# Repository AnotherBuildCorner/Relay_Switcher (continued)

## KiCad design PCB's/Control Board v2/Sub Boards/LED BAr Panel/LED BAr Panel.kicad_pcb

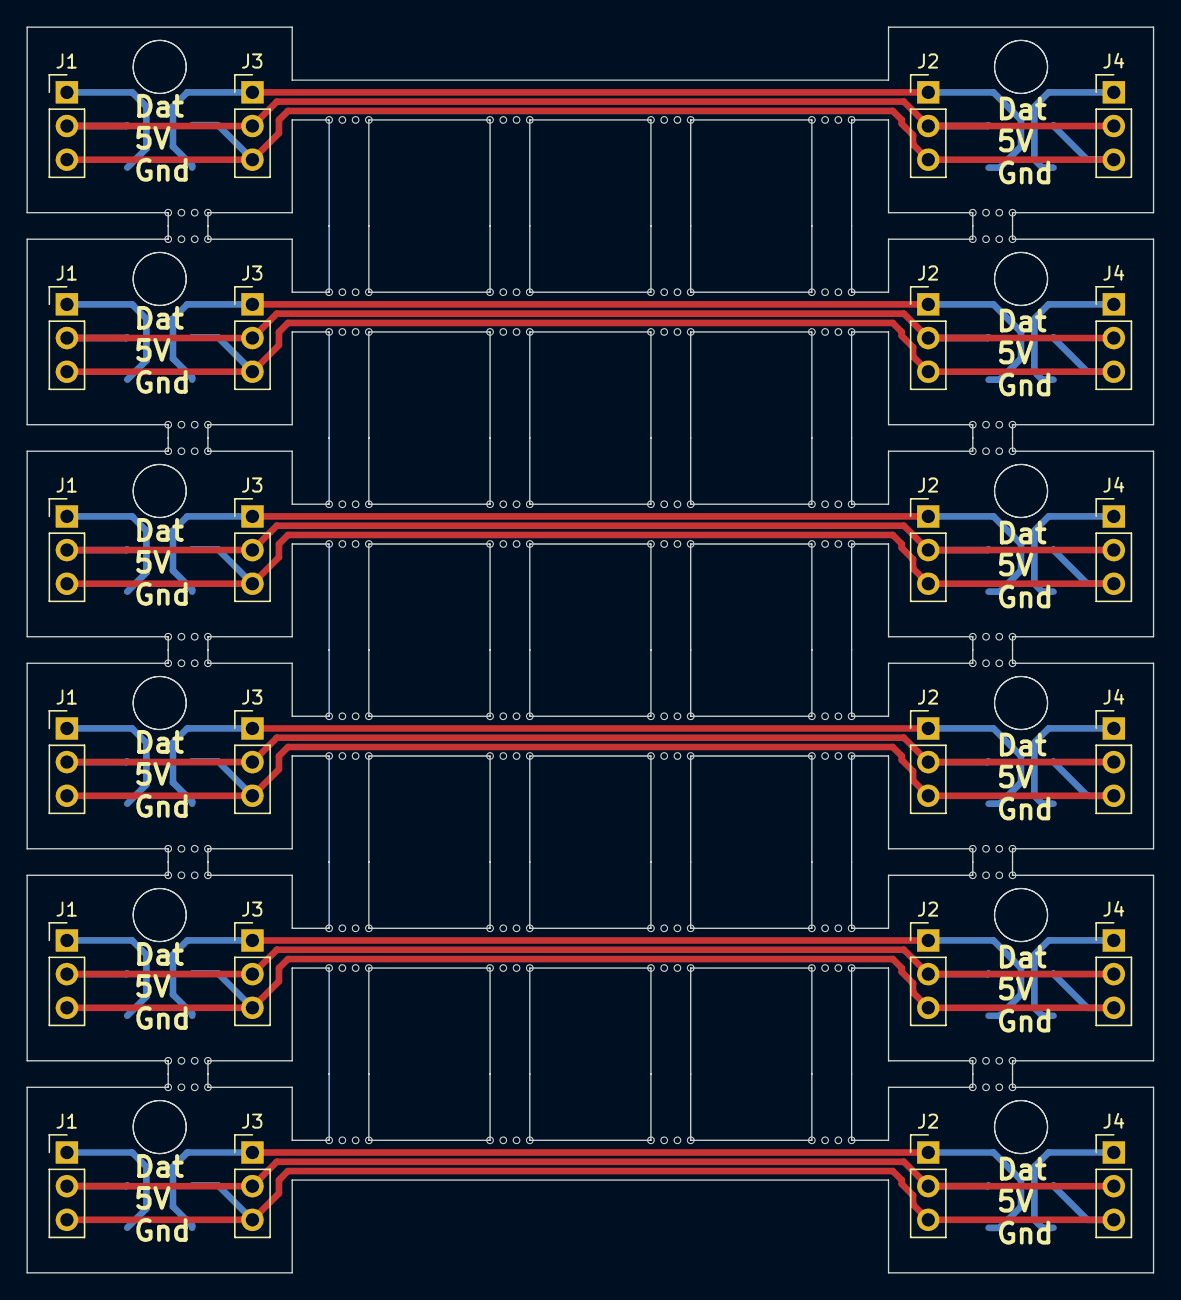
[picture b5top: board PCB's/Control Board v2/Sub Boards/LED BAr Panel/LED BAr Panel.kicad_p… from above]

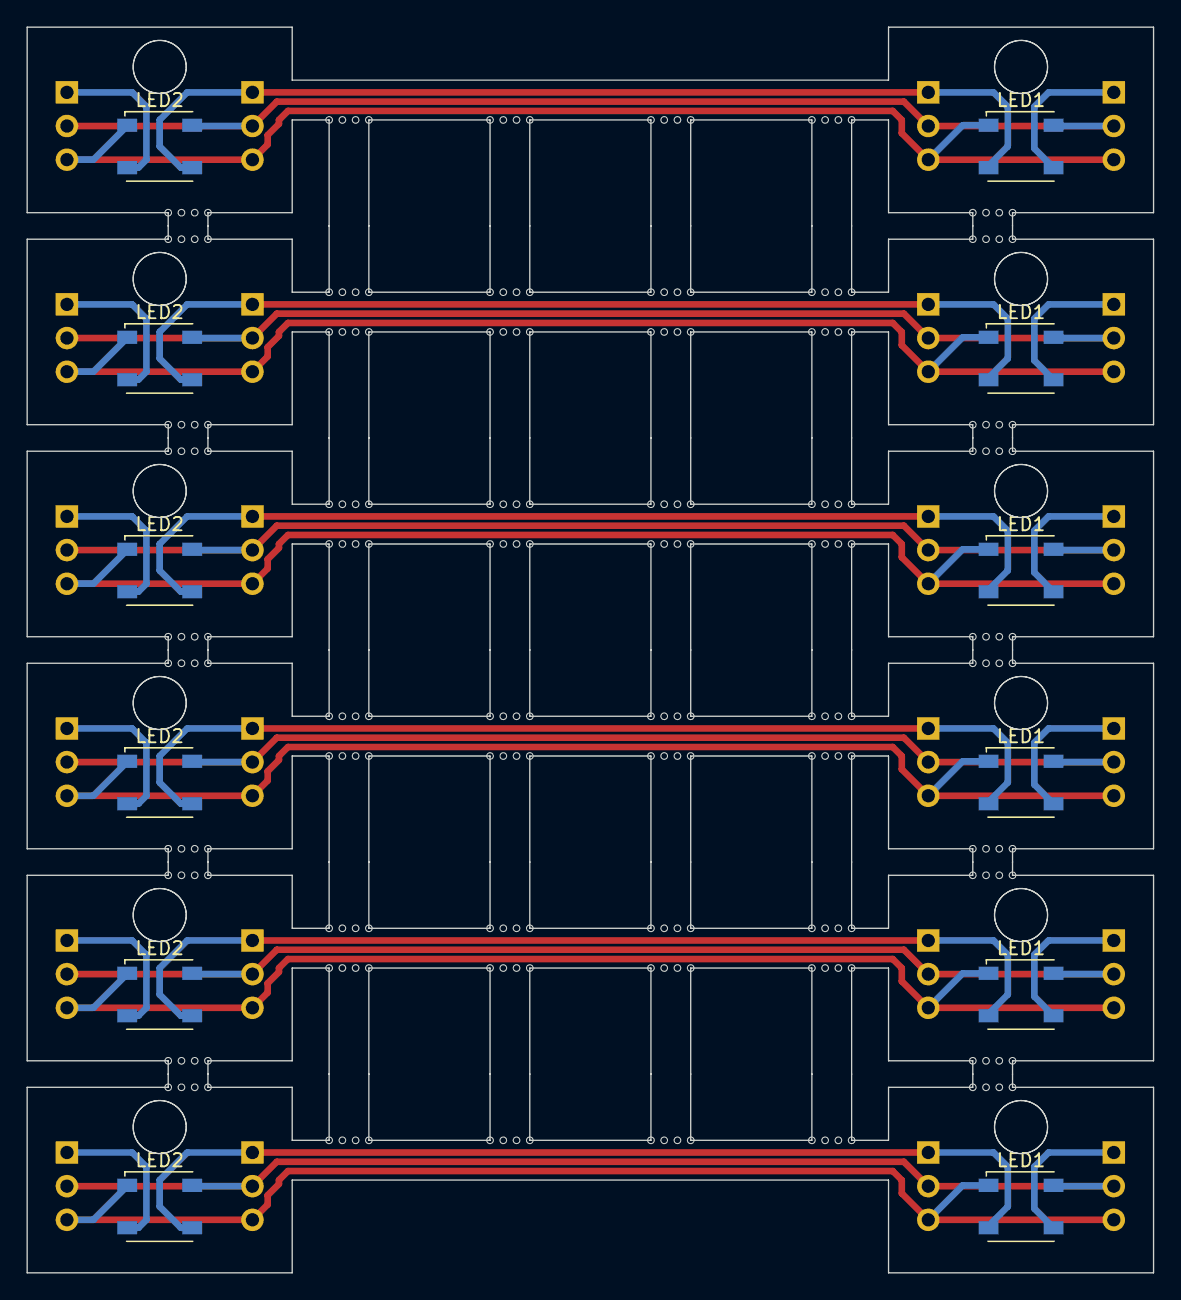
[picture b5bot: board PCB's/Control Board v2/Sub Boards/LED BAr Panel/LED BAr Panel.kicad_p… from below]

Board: 2 copper layers, 85.0 x 94.0 mm, 276 parts (12 on the bottom side), 30 nets.

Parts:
J1, J1#2, J1#3, J1#4, J1#5, J1#6, J3, J3#2, J3#3, J3#4, J3#5, J3#6: LED Strip Conn; PinHeader_1x03_P2.54mm_Vertical
J2, J2#2, J2#3, J2#4, J2#5, J2#6, J4, J4#2, J4#3, J4#4, J4#5, J4#6: Conn_01x03_Socket; PinHeader_1x03_P2.54mm_Vertical
KiKit_MB_1_1, KiKit_MB_1_2, KiKit_MB_1_3, KiKit_MB_1_4, KiKit_MB_2_1, KiKit_MB_2_2, KiKit_MB_2_3, KiKit_MB_2_4, KiKit_MB_3_1, KiKit_MB_3_2, KiKit_MB_3_3, KiKit_MB_3_4, KiKit_MB_4_1, KiKit_MB_4_2, KiKit_MB_4_3, KiKit_MB_4_4, KiKit_MB_5_1, KiKit_MB_5_2, KiKit_MB_5_3, KiKit_MB_5_4, KiKit_MB_6_1, KiKit_MB_6_2, KiKit_MB_6_3, KiKit_MB_6_4, KiKit_MB_7_1, KiKit_MB_7_2, KiKit_MB_7_3, KiKit_MB_7_4, KiKit_MB_8_1, KiKit_MB_8_2, KiKit_MB_8_3, KiKit_MB_8_4, KiKit_MB_9_1, KiKit_MB_9_2, KiKit_MB_9_3, KiKit_MB_9_4, KiKit_MB_10_1, KiKit_MB_10_2, KiKit_MB_10_3, KiKit_MB_10_4, KiKit_MB_11_1, KiKit_MB_11_2, KiKit_MB_11_3, KiKit_MB_11_4, KiKit_MB_12_1, KiKit_MB_12_2, KiKit_MB_12_3, KiKit_MB_12_4, KiKit_MB_13_1, KiKit_MB_13_2, KiKit_MB_13_3, KiKit_MB_13_4, KiKit_MB_14_1, KiKit_MB_14_2, KiKit_MB_14_3, KiKit_MB_14_4, KiKit_MB_15_1, KiKit_MB_15_2, KiKit_MB_15_3, KiKit_MB_15_4, KiKit_MB_16_1, KiKit_MB_16_2, KiKit_MB_16_3, KiKit_MB_16_4, KiKit_MB_17_1, KiKit_MB_17_2, KiKit_MB_17_3, KiKit_MB_17_4, KiKit_MB_18_1, KiKit_MB_18_2, KiKit_MB_18_3, KiKit_MB_18_4, KiKit_MB_19_1, KiKit_MB_19_2, KiKit_MB_19_3, KiKit_MB_19_4, KiKit_MB_20_1, KiKit_MB_20_2, KiKit_MB_20_3, KiKit_MB_20_4, KiKit_MB_21_1, KiKit_MB_21_2, KiKit_MB_21_3, KiKit_MB_21_4, KiKit_MB_22_1, KiKit_MB_22_2, KiKit_MB_22_3, KiKit_MB_22_4, KiKit_MB_23_1, KiKit_MB_23_2, KiKit_MB_23_3, KiKit_MB_23_4, KiKit_MB_24_1, KiKit_MB_24_2, KiKit_MB_24_3, KiKit_MB_24_4, KiKit_MB_25_1, KiKit_MB_25_2, KiKit_MB_25_3, KiKit_MB_25_4, KiKit_MB_26_1, KiKit_MB_26_2, KiKit_MB_26_3, KiKit_MB_26_4, KiKit_MB_27_1, KiKit_MB_27_2, KiKit_MB_27_3, KiKit_MB_27_4, KiKit_MB_28_1, KiKit_MB_28_2, KiKit_MB_28_3, KiKit_MB_28_4, KiKit_MB_29_1, KiKit_MB_29_2, KiKit_MB_29_3, KiKit_MB_29_4, KiKit_MB_30_1, KiKit_MB_30_2, KiKit_MB_30_3, KiKit_MB_30_4, KiKit_MB_31_1, KiKit_MB_31_2, KiKit_MB_31_3, KiKit_MB_31_4, KiKit_MB_32_1, KiKit_MB_32_2, KiKit_MB_32_3, KiKit_MB_32_4, KiKit_MB_33_1, KiKit_MB_33_2, KiKit_MB_33_3, KiKit_MB_33_4, KiKit_MB_34_1, KiKit_MB_34_2, KiKit_MB_34_3, KiKit_MB_34_4, KiKit_MB_35_1, KiKit_MB_35_2, KiKit_MB_35_3, KiKit_MB_35_4, KiKit_MB_36_1, KiKit_MB_36_2, KiKit_MB_36_3, KiKit_MB_36_4, KiKit_MB_37_1, KiKit_MB_37_2, KiKit_MB_37_3, KiKit_MB_37_4, KiKit_MB_38_1, KiKit_MB_38_2, KiKit_MB_38_3, KiKit_MB_38_4, KiKit_MB_39_1, KiKit_MB_39_2, KiKit_MB_39_3, KiKit_MB_39_4, KiKit_MB_40_1, KiKit_MB_40_2, KiKit_MB_40_3, KiKit_MB_40_4, KiKit_MB_41_1, KiKit_MB_41_2, KiKit_MB_41_3, KiKit_MB_41_4, KiKit_MB_42_1, KiKit_MB_42_2, KiKit_MB_42_3, KiKit_MB_42_4, KiKit_MB_43_1, KiKit_MB_43_2, KiKit_MB_43_3, KiKit_MB_43_4, KiKit_MB_44_1, KiKit_MB_44_2, KiKit_MB_44_3, KiKit_MB_44_4, KiKit_MB_45_1, KiKit_MB_45_2, KiKit_MB_45_3, KiKit_MB_45_4, KiKit_MB_46_1, KiKit_MB_46_2, KiKit_MB_46_3, KiKit_MB_46_4, KiKit_MB_47_1, KiKit_MB_47_2, KiKit_MB_47_3, KiKit_MB_47_4, KiKit_MB_48_1, KiKit_MB_48_2, KiKit_MB_48_3, KiKit_MB_48_4, KiKit_MB_49_1, KiKit_MB_49_2, KiKit_MB_49_3, KiKit_MB_49_4, KiKit_MB_50_1, KiKit_MB_50_2, KiKit_MB_50_3, KiKit_MB_50_4, KiKit_MB_51_1, KiKit_MB_51_2, KiKit_MB_51_3, KiKit_MB_51_4, KiKit_MB_52_1, KiKit_MB_52_2, KiKit_MB_52_3, KiKit_MB_52_4, KiKit_MB_53_1, KiKit_MB_53_2, KiKit_MB_53_3, KiKit_MB_53_4, KiKit_MB_54_1, KiKit_MB_54_2, KiKit_MB_54_3, KiKit_MB_54_4, KiKit_MB_55_1, KiKit_MB_55_2, KiKit_MB_55_3, KiKit_MB_55_4, KiKit_MB_56_1, KiKit_MB_56_2, KiKit_MB_56_3, KiKit_MB_56_4, KiKit_MB_57_1, KiKit_MB_57_2, KiKit_MB_57_3, KiKit_MB_57_4, KiKit_MB_58_1, KiKit_MB_58_2, KiKit_MB_58_3, KiKit_MB_58_4, KiKit_MB_59_1, KiKit_MB_59_2, KiKit_MB_59_3, KiKit_MB_59_4, KiKit_MB_60_1, KiKit_MB_60_2, KiKit_MB_60_3, KiKit_MB_60_4: NPTH
LED1, LED1#2, LED1#3, LED1#4, LED1#5, LED1#6, LED2, LED2#2, LED2#3, LED2#4, LED2#5, LED2#6: IN-PI55TATPRPGPB; LED_Inolux_IN-PI554FCH_PLCC4_5.0x5.0mm_P3.2mm

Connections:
Board_0-+5V: J1#5.2, J2#6.2, J3#6.2, J4#2.2, LED1#4.4 (VDD), LED2#6.4 (VDD)
Board_0-/A: J2#6.1, J3#6.1, LED1#4.2 (DOUT), LED2#6.3 (DIN)
Board_0-/B: J4#2.1, LED2#6.2 (DOUT)
Board_0-GND: J1#5.3, J2#6.3, J3#6.3, J4#2.3, LED1#4.1 (GND), LED2#6.1 (GND)
Board_0-Net-(J1-Pin_1): J1#5.1, LED1#4.3 (DIN)
Board_1-+5V: J1#3.2, J2#5.2, J3.2, J4#3.2, LED1#5.4 (VDD), LED2#3.4 (VDD)
Board_1-/A: J2#5.1, J3.1, LED1#5.2 (DOUT), LED2#3.3 (DIN)
Board_1-/B: J4#3.1, LED2#3.2 (DOUT)
Board_1-GND: J1#3.3, J2#5.3, J3.3, J4#3.3, LED1#5.1 (GND), LED2#3.1 (GND)
Board_1-Net-(J1-Pin_1): J1#3.1, LED1#5.3 (DIN)
Board_2-+5V: J1#2.2, J2#4.2, J3#2.2, J4#6.2, LED1#2.4 (VDD), LED2#5.4 (VDD)
Board_2-/A: J2#4.1, J3#2.1, LED1#2.2 (DOUT), LED2#5.3 (DIN)
Board_2-/B: J4#6.1, LED2#5.2 (DOUT)
Board_2-GND: J1#2.3, J2#4.3, J3#2.3, J4#6.3, LED1#2.1 (GND), LED2#5.1 (GND)
Board_2-Net-(J1-Pin_1): J1#2.1, LED1#2.3 (DIN)
Board_3-+5V: J1#6.2, J2#3.2, J3#3.2, J4#4.2, LED1#6.4 (VDD), LED2#2.4 (VDD)
Board_3-/A: J2#3.1, J3#3.1, LED1#6.2 (DOUT), LED2#2.3 (DIN)
Board_3-/B: J4#4.1, LED2#2.2 (DOUT)
Board_3-GND: J1#6.3, J2#3.3, J3#3.3, J4#4.3, LED1#6.1 (GND), LED2#2.1 (GND)
Board_3-Net-(J1-Pin_1): J1#6.1, LED1#6.3 (DIN)
Board_4-+5V: J1#4.2, J2.2, J3#4.2, J4#5.2, LED1.4 (VDD), LED2.4 (VDD)
Board_4-/A: J2.1, J3#4.1, LED1.2 (DOUT), LED2.3 (DIN)
Board_4-/B: J4#5.1, LED2.2 (DOUT)
Board_4-GND: J1#4.3, J2.3, J3#4.3, J4#5.3, LED1.1 (GND), LED2.1 (GND)
Board_4-Net-(J1-Pin_1): J1#4.1, LED1.3 (DIN)
Board_5-+5V: J1.2, J2#2.2, J3#5.2, J4.2, LED1#3.4 (VDD), LED2#4.4 (VDD)
Board_5-/A: J2#2.1, J3#5.1, LED1#3.2 (DOUT), LED2#4.3 (DIN)
Board_5-/B: J4.1, LED2#4.2 (DOUT)
Board_5-GND: J1.3, J2#2.3, J3#5.3, J4.3, LED1#3.1 (GND), LED2#4.1 (GND)
Board_5-Net-(J1-Pin_1): J1.1, LED1#3.3 (DIN)

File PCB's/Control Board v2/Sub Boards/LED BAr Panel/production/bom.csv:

Designator,Footprint,Quantity,Value,LCSC Part #
"J1_6, J1_5, J1_4, J1_3, J1_2, J1, J3_6, J3_5, J3_4, J3_3, J3_2, J3",PinHeader_1x03_P2.54mm_Vertical,12,LED Strip Conn,
"J2_6, J2_5, J2_4, J2_3, J2_2, J2, J4_6, J4_5, J4_4, J4_3, J4_2, J4",PinHeader_1x03_P2.54mm_Vertical,12,Conn_01x03_Socket,
"KiKit_MB_10_1, KiKit_MB_10_2, KiKit_MB_10_3, KiKit_MB_10_4, KiKit_MB_11_1, KiKit_MB_11_2, KiKit_MB_11_3, KiKit_MB_11_4, KiKit_MB_12_1, KiKit_MB_12_2, KiKit_MB_12_3, KiKit_MB_12_4, KiKit_MB_13_1, KiKit_MB_13_2, KiKit_MB_13_3, KiKit_MB_13_4, KiKit_MB_14_1, KiKit_MB_14_2, KiKit_MB_14_3, KiKit_MB_14_4, KiKit_MB_15_1, KiKit_MB_15_2, KiKit_MB_15_3, KiKit_MB_15_4, KiKit_MB_16_1, KiKit_MB_16_2, KiKit_MB_16_3, KiKit_MB_16_4, KiKit_MB_17_1, KiKit_MB_17_2, KiKit_MB_17_3, KiKit_MB_17_4, KiKit_MB_18_1, KiKit_MB_18_2, KiKit_MB_18_3, KiKit_MB_18_4, KiKit_MB_19_1, KiKit_MB_19_2, KiKit_MB_19_3, KiKit_MB_19_4, KiKit_MB_1_1, KiKit_MB_1_2, KiKit_MB_1_3, KiKit_MB_1_4, KiKit_MB_20_1, KiKit_MB_20_2, KiKit_MB_20_3, KiKit_MB_20_4, KiKit_MB_21_1, KiKit_MB_21_2, KiKit_MB_21_3, KiKit_MB_21_4, KiKit_MB_22_1, KiKit_MB_22_2, KiKit_MB_22_3, KiKit_MB_22_4, KiKit_MB_23_1, KiKit_MB_23_2, KiKit_MB_23_3, KiKit_MB_23_4, KiKit_MB_24_1, KiKit_MB_24_2, KiKit_MB_24_3, KiKit_MB_24_4, KiKit_MB_25_1, KiKit_MB_25_2, KiKit_MB_25_3, KiKit_MB_25_4, KiKit_MB_26_1, KiKit_MB_26_2, KiKit_MB_26_3, KiKit_MB_26_4, KiKit_MB_27_1, KiKit_MB_27_2, KiKit_MB_27_3, KiKit_MB_27_4, KiKit_MB_28_1, KiKit_MB_28_2, KiKit_MB_28_3, KiKit_MB_28_4, KiKit_MB_29_1, KiKit_MB_29_2, KiKit_MB_29_3, KiKit_MB_29_4, KiKit_MB_2_1, KiKit_MB_2_2, KiKit_MB_2_3, KiKit_MB_2_4, KiKit_MB_30_1, KiKit_MB_30_2, KiKit_MB_30_3, KiKit_MB_30_4, KiKit_MB_31_1, KiKit_MB_31_2, KiKit_MB_31_3, KiKit_MB_31_4, KiKit_MB_32_1, KiKit_MB_32_2, KiKit_MB_32_3, KiKit_MB_32_4, KiKit_MB_33_1, KiKit_MB_33_2, KiKit_MB_33_3, KiKit_MB_33_4, KiKit_MB_34_1, KiKit_MB_34_2, KiKit_MB_34_3, KiKit_MB_34_4, KiKit_MB_35_1, KiKit_MB_35_2, KiKit_MB_35_3, KiKit_MB_35_4, KiKit_MB_36_1, KiKit_MB_36_2, KiKit_MB_36_3, KiKit_MB_36_4, KiKit_MB_37_1, KiKit_MB_37_2, KiKit_MB_37_3, KiKit_MB_37_4, KiKit_MB_38_1, KiKit_MB_38_2, KiKit_MB_38_3, KiKit_MB_38_4, KiKit_MB_39_1, KiKit_MB_39_2, KiKit_MB_39_3, KiKit_MB_39_4, KiKit_MB_3_1, KiKit_MB_3_2, KiKit_MB_3_3, KiKit_MB_3_4, KiKit_MB_40_1, KiKit_MB_40_2, KiKit_MB_40_3, KiKit_MB_40_4, KiKit_MB_41_1, KiKit_MB_41_2, KiKit_MB_41_3, KiKit_MB_41_4, KiKit_MB_42_1, KiKit_MB_42_2, KiKit_MB_42_3, KiKit_MB_42_4, KiKit_MB_43_1, KiKit_MB_43_2, KiKit_MB_43_3, KiKit_MB_43_4, KiKit_MB_44_1, KiKit_MB_44_2, KiKit_MB_44_3, KiKit_MB_44_4, KiKit_MB_45_1, KiKit_MB_45_2, KiKit_MB_45_3, KiKit_MB_45_4, KiKit_MB_46_1, KiKit_MB_46_2, KiKit_MB_46_3, KiKit_MB_46_4, KiKit_MB_47_1, KiKit_MB_47_2, KiKit_MB_47_3, KiKit_MB_47_4, KiKit_MB_48_1, KiKit_MB_48_2, KiKit_MB_48_3, KiKit_MB_48_4, KiKit_MB_49_1, KiKit_MB_49_2, KiKit_MB_49_3, KiKit_MB_49_4, KiKit_MB_4_1, KiKit_MB_4_2, KiKit_MB_4_3, KiKit_MB_4_4, KiKit_MB_50_1, KiKit_MB_50_2, KiKit_MB_50_3, KiKit_MB_50_4, KiKit_MB_51_1, KiKit_MB_51_2, KiKit_MB_51_3, KiKit_MB_51_4, KiKit_MB_52_1, KiKit_MB_52_2, KiKit_MB_52_3, KiKit_MB_52_4, KiKit_MB_53_1, KiKit_MB_53_2, KiKit_MB_53_3, KiKit_MB_53_4, KiKit_MB_54_1, KiKit_MB_54_2, KiKit_MB_54_3, KiKit_MB_54_4, KiKit_MB_55_1, KiKit_MB_55_2, KiKit_MB_55_3, KiKit_MB_55_4",NPTH,200,NPTH,
"KiKit_MB_56_1, KiKit_MB_56_2, KiKit_MB_56_3, KiKit_MB_56_4, KiKit_MB_57_1, KiKit_MB_57_2, KiKit_MB_57_3, KiKit_MB_57_4, KiKit_MB_58_1, KiKit_MB_58_2, KiKit_MB_58_3, KiKit_MB_58_4, KiKit_MB_59_1, KiKit_MB_59_2, KiKit_MB_59_3, KiKit_MB_59_4, KiKit_MB_5_1, KiKit_MB_5_2, KiKit_MB_5_3, KiKit_MB_5_4, KiKit_MB_60_1, KiKit_MB_60_2, KiKit_MB_60_3, KiKit_MB_60_4, KiKit_MB_6_1, KiKit_MB_6_2, KiKit_MB_6_3, KiKit_MB_6_4, KiKit_MB_7_1, KiKit_MB_7_2, KiKit_MB_7_3, KiKit_MB_7_4, KiKit_MB_8_1, KiKit_MB_8_2, KiKit_MB_8_3, KiKit_MB_8_4, KiKit_MB_9_1, KiKit_MB_9_2, KiKit_MB_9_3, KiKit_MB_9_4",NPTH,40,NPTH,
"LED1_6, LED1_5, LED1_4, LED1_3, LED1_2, LED1, LED2_6, LED2_5, LED2_4, LED2_3, LED2_2, LED2",LED_Inolux_IN-PI554FCH_PLCC4_5.0x5.0mm_P3.2mm,12,IN-PI55TATPRPGPB,

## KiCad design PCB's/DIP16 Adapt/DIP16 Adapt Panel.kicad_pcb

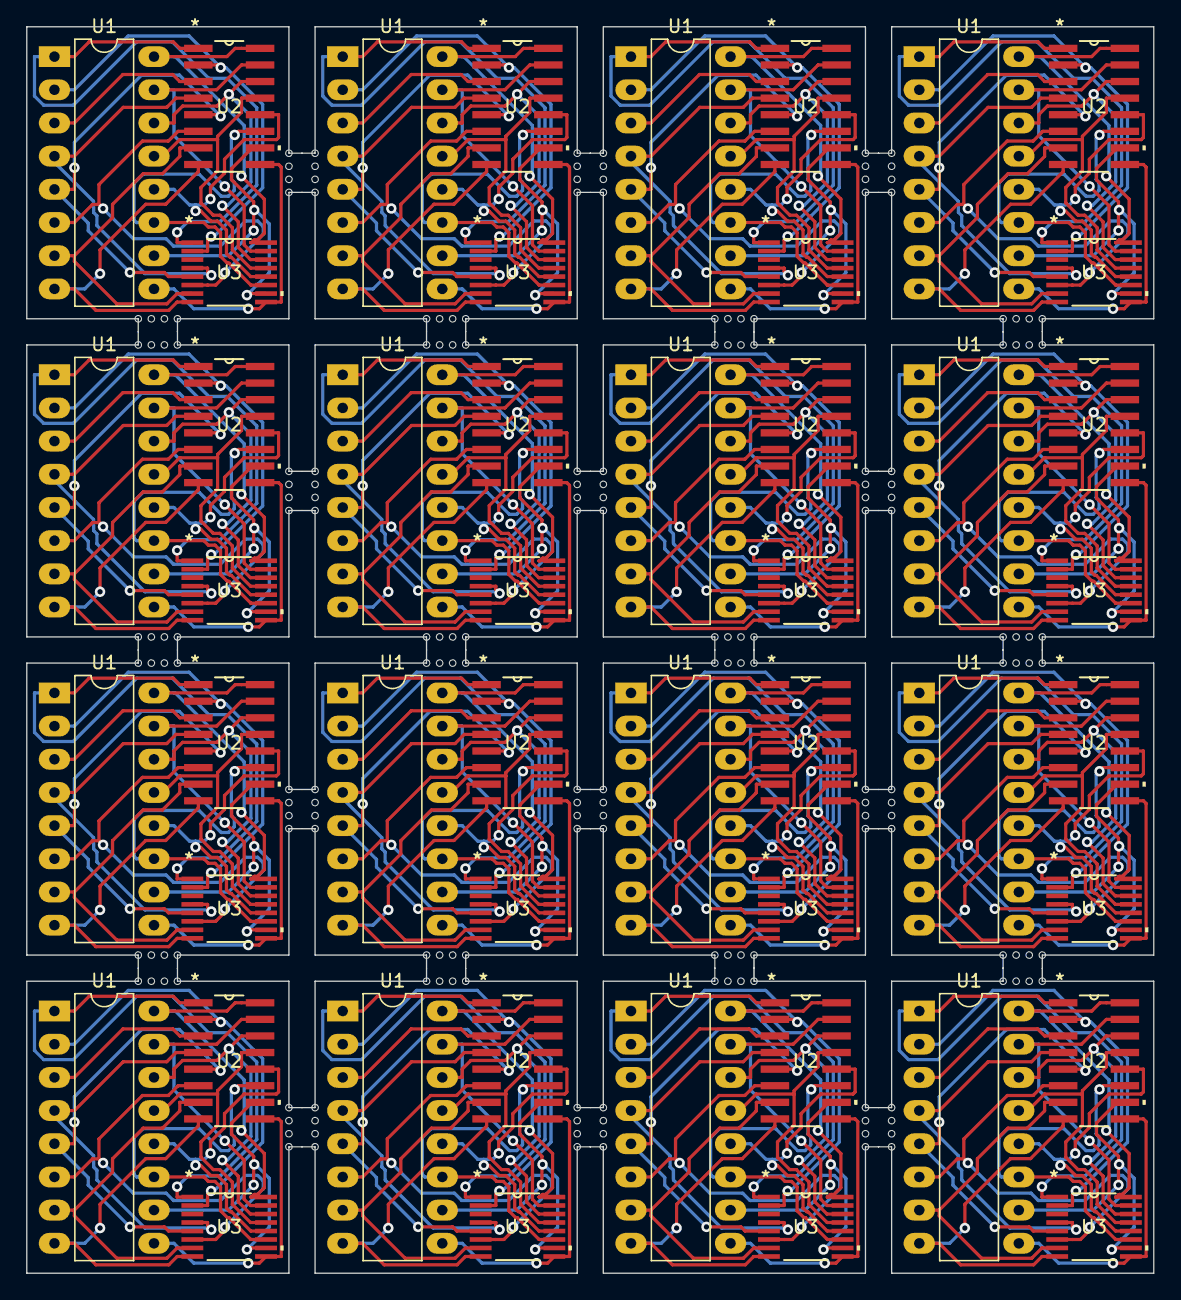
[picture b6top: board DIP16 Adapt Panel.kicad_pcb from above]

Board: 2 copper layers, 86.3 x 95.4 mm, 240 parts (0 on the bottom side), 256 nets.

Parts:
KiKit_MB_1_1, KiKit_MB_1_2, KiKit_MB_1_3, KiKit_MB_1_4, KiKit_MB_2_1, KiKit_MB_2_2, KiKit_MB_2_3, KiKit_MB_2_4, KiKit_MB_3_1, KiKit_MB_3_2, KiKit_MB_3_3, KiKit_MB_3_4, KiKit_MB_4_1, KiKit_MB_4_2, KiKit_MB_4_3, KiKit_MB_4_4, KiKit_MB_5_1, KiKit_MB_5_2, KiKit_MB_5_3, KiKit_MB_5_4, KiKit_MB_6_1, KiKit_MB_6_2, KiKit_MB_6_3, KiKit_MB_6_4, KiKit_MB_7_1, KiKit_MB_7_2, KiKit_MB_7_3, KiKit_MB_7_4, KiKit_MB_8_1, KiKit_MB_8_2, KiKit_MB_8_3, KiKit_MB_8_4, KiKit_MB_9_1, KiKit_MB_9_2, KiKit_MB_9_3, KiKit_MB_9_4, KiKit_MB_10_1, KiKit_MB_10_2, KiKit_MB_10_3, KiKit_MB_10_4, KiKit_MB_11_1, KiKit_MB_11_2, KiKit_MB_11_3, KiKit_MB_11_4, KiKit_MB_12_1, KiKit_MB_12_2, KiKit_MB_12_3, KiKit_MB_12_4, KiKit_MB_13_1, KiKit_MB_13_2, KiKit_MB_13_3, KiKit_MB_13_4, KiKit_MB_14_1, KiKit_MB_14_2, KiKit_MB_14_3, KiKit_MB_14_4, KiKit_MB_15_1, KiKit_MB_15_2, KiKit_MB_15_3, KiKit_MB_15_4, KiKit_MB_16_1, KiKit_MB_16_2, KiKit_MB_16_3, KiKit_MB_16_4, KiKit_MB_17_1, KiKit_MB_17_2, KiKit_MB_17_3, KiKit_MB_17_4, KiKit_MB_18_1, KiKit_MB_18_2, KiKit_MB_18_3, KiKit_MB_18_4, KiKit_MB_19_1, KiKit_MB_19_2, KiKit_MB_19_3, KiKit_MB_19_4, KiKit_MB_20_1, KiKit_MB_20_2, KiKit_MB_20_3, KiKit_MB_20_4, KiKit_MB_21_1, KiKit_MB_21_2, KiKit_MB_21_3, KiKit_MB_21_4, KiKit_MB_22_1, KiKit_MB_22_2, KiKit_MB_22_3, KiKit_MB_22_4, KiKit_MB_23_1, KiKit_MB_23_2, KiKit_MB_23_3, KiKit_MB_23_4, KiKit_MB_24_1, KiKit_MB_24_2, KiKit_MB_24_3, KiKit_MB_24_4, KiKit_MB_25_1, KiKit_MB_25_2, KiKit_MB_25_3, KiKit_MB_25_4, KiKit_MB_26_1, KiKit_MB_26_2, KiKit_MB_26_3, KiKit_MB_26_4, KiKit_MB_27_1, KiKit_MB_27_2, KiKit_MB_27_3, KiKit_MB_27_4, KiKit_MB_28_1, KiKit_MB_28_2, KiKit_MB_28_3, KiKit_MB_28_4, KiKit_MB_29_1, KiKit_MB_29_2, KiKit_MB_29_3, KiKit_MB_29_4, KiKit_MB_30_1, KiKit_MB_30_2, KiKit_MB_30_3, KiKit_MB_30_4, KiKit_MB_31_1, KiKit_MB_31_2, KiKit_MB_31_3, KiKit_MB_31_4, KiKit_MB_32_1, KiKit_MB_32_2, KiKit_MB_32_3, KiKit_MB_32_4, KiKit_MB_33_1, KiKit_MB_33_2, KiKit_MB_33_3, KiKit_MB_33_4, KiKit_MB_34_1, KiKit_MB_34_2, KiKit_MB_34_3, KiKit_MB_34_4, KiKit_MB_35_1, KiKit_MB_35_2, KiKit_MB_35_3, KiKit_MB_35_4, KiKit_MB_36_1, KiKit_MB_36_2, KiKit_MB_36_3, KiKit_MB_36_4, KiKit_MB_37_1, KiKit_MB_37_2, KiKit_MB_37_3, KiKit_MB_37_4, KiKit_MB_38_1, KiKit_MB_38_2, KiKit_MB_38_3, KiKit_MB_38_4, KiKit_MB_39_1, KiKit_MB_39_2, KiKit_MB_39_3, KiKit_MB_39_4, KiKit_MB_40_1, KiKit_MB_40_2, KiKit_MB_40_3, KiKit_MB_40_4, KiKit_MB_41_1, KiKit_MB_41_2, KiKit_MB_41_3, KiKit_MB_41_4, KiKit_MB_42_1, KiKit_MB_42_2, KiKit_MB_42_3, KiKit_MB_42_4, KiKit_MB_43_1, KiKit_MB_43_2, KiKit_MB_43_3, KiKit_MB_43_4, KiKit_MB_44_1, KiKit_MB_44_2, KiKit_MB_44_3, KiKit_MB_44_4, KiKit_MB_45_1, KiKit_MB_45_2, KiKit_MB_45_3, KiKit_MB_45_4, KiKit_MB_46_1, KiKit_MB_46_2, KiKit_MB_46_3, KiKit_MB_46_4, KiKit_MB_47_1, KiKit_MB_47_2, KiKit_MB_47_3, KiKit_MB_47_4, KiKit_MB_48_1, KiKit_MB_48_2, KiKit_MB_48_3, KiKit_MB_48_4: NPTH
U1, U1#2, U1#3, U1#4, U1#5, U1#6, U1#7, U1#8, U1#9, U1#10, U1#11, U1#12, U1#13, U1#14, U1#15, U1#16: CD74HC4051M96; DIP-16_W7.62mm_LongPads
U2, U2#2, U2#3, U2#4, U2#5, U2#6, U2#7, U2#8, U2#9, U2#10, U2#11, U2#12, U2#13, U2#14, U2#15, U2#16: CD74HC4051M96; D16
U3, U3#2, U3#3, U3#4, U3#5, U3#6, U3#7, U3#8, U3#9, U3#10, U3#11, U3#12, U3#13, U3#14, U3#15, U3#16: CD74HC4051M96; PW16

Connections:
Board_0-Net-(U1-*E): U1#5.6 (*E), U2#8.6 (*E), U3#13.6 (*E)
Board_0-Net-(U1-A0): U1#5.13 (A0), U2#8.13 (A0), U3#13.13 (A0)
Board_0-Net-(U1-A1): U1#5.14 (A1), U2#8.14 (A1), U3#13.14 (A1)
Board_0-Net-(U1-A2): U1#5.15 (A2), U2#8.15 (A2), U3#13.15 (A2)
Board_0-Net-(U1-A3): U1#5.12 (A3), U2#8.12 (A3), U3#13.12 (A3)
Board_0-Net-(U1-A4): U1#5.1 (A4), U2#8.1 (A4), U3#13.1 (A4)
Board_0-Net-(U1-A5): U1#5.5 (A5), U2#8.5 (A5), U3#13.5 (A5)
Board_0-Net-(U1-A6): U1#5.2 (A6), U2#8.2 (A6), U3#13.2 (A6)
Board_0-Net-(U1-A7): U1#5.4 (A7), U2#8.4 (A7), U3#13.4 (A7)
Board_0-Net-(U1-A): U1#5.3 (A), U2#8.3 (A), U3#13.3 (A)
Board_0-Net-(U1-GND): U1#5.8 (GND), U2#8.8 (GND), U3#13.8 (GND)
Board_0-Net-(U1-S0): U1#5.11 (S0), U2#8.11 (S0), U3#13.11 (S0)
Board_0-Net-(U1-S1): U1#5.10 (S1), U2#8.10 (S1), U3#13.10 (S1)
Board_0-Net-(U1-S2): U1#5.9 (S2), U2#8.9 (S2), U3#13.9 (S2)
Board_0-Net-(U1-VCC): U1#5.16 (VCC), U2#8.16 (VCC), U3#13.16 (VCC)
Board_0-Net-(U1-VEE): U1#5.7 (VEE), U2#8.7 (VEE), U3#13.7 (VEE)
Board_1-Net-(U1-*E): U1#10.6 (*E), U2#9.6 (*E), U3#6.6 (*E)
Board_1-Net-(U1-A0): U1#10.13 (A0), U2#9.13 (A0), U3#6.13 (A0)
Board_1-Net-(U1-A1): U1#10.14 (A1), U2#9.14 (A1), U3#6.14 (A1)
Board_1-Net-(U1-A2): U1#10.15 (A2), U2#9.15 (A2), U3#6.15 (A2)
Board_1-Net-(U1-A3): U1#10.12 (A3), U2#9.12 (A3), U3#6.12 (A3)
Board_1-Net-(U1-A4): U1#10.1 (A4), U2#9.1 (A4), U3#6.1 (A4)
Board_1-Net-(U1-A5): U1#10.5 (A5), U2#9.5 (A5), U3#6.5 (A5)
Board_1-Net-(U1-A6): U1#10.2 (A6), U2#9.2 (A6), U3#6.2 (A6)
Board_1-Net-(U1-A7): U1#10.4 (A7), U2#9.4 (A7), U3#6.4 (A7)
Board_1-Net-(U1-A): U1#10.3 (A), U2#9.3 (A), U3#6.3 (A)
Board_1-Net-(U1-GND): U1#10.8 (GND), U2#9.8 (GND), U3#6.8 (GND)
Board_1-Net-(U1-S0): U1#10.11 (S0), U2#9.11 (S0), U3#6.11 (S0)
Board_1-Net-(U1-S1): U1#10.10 (S1), U2#9.10 (S1), U3#6.10 (S1)
Board_1-Net-(U1-S2): U1#10.9 (S2), U2#9.9 (S2), U3#6.9 (S2)
Board_1-Net-(U1-VCC): U1#10.16 (VCC), U2#9.16 (VCC), U3#6.16 (VCC)
Board_1-Net-(U1-VEE): U1#10.7 (VEE), U2#9.7 (VEE), U3#6.7 (VEE)
Board_2-Net-(U1-*E): U1#16.6 (*E), U2#14.6 (*E), U3.6 (*E)
Board_2-Net-(U1-A0): U1#16.13 (A0), U2#14.13 (A0), U3.13 (A0)
Board_2-Net-(U1-A1): U1#16.14 (A1), U2#14.14 (A1), U3.14 (A1)
Board_2-Net-(U1-A2): U1#16.15 (A2), U2#14.15 (A2), U3.15 (A2)
Board_2-Net-(U1-A3): U1#16.12 (A3), U2#14.12 (A3), U3.12 (A3)
Board_2-Net-(U1-A4): U1#16.1 (A4), U2#14.1 (A4), U3.1 (A4)
Board_2-Net-(U1-A5): U1#16.5 (A5), U2#14.5 (A5), U3.5 (A5)
Board_2-Net-(U1-A6): U1#16.2 (A6), U2#14.2 (A6), U3.2 (A6)
Board_2-Net-(U1-A7): U1#16.4 (A7), U2#14.4 (A7), U3.4 (A7)
Board_2-Net-(U1-A): U1#16.3 (A), U2#14.3 (A), U3.3 (A)
Board_2-Net-(U1-GND): U1#16.8 (GND), U2#14.8 (GND), U3.8 (GND)
Board_2-Net-(U1-S0): U1#16.11 (S0), U2#14.11 (S0), U3.11 (S0)
Board_2-Net-(U1-S1): U1#16.10 (S1), U2#14.10 (S1), U3.10 (S1)
Board_2-Net-(U1-S2): U1#16.9 (S2), U2#14.9 (S2), U3.9 (S2)
Board_2-Net-(U1-VCC): U1#16.16 (VCC), U2#14.16 (VCC), U3.16 (VCC)
Board_2-Net-(U1-VEE): U1#16.7 (VEE), U2#14.7 (VEE), U3.7 (VEE)
Board_3-Net-(U1-*E): U1#2.6 (*E), U2#12.6 (*E), U3#11.6 (*E)
Board_3-Net-(U1-A0): U1#2.13 (A0), U2#12.13 (A0), U3#11.13 (A0)
Board_3-Net-(U1-A1): U1#2.14 (A1), U2#12.14 (A1), U3#11.14 (A1)
Board_3-Net-(U1-A2): U1#2.15 (A2), U2#12.15 (A2), U3#11.15 (A2)
Board_3-Net-(U1-A3): U1#2.12 (A3), U2#12.12 (A3), U3#11.12 (A3)
Board_3-Net-(U1-A4): U1#2.1 (A4), U2#12.1 (A4), U3#11.1 (A4)
Board_3-Net-(U1-A5): U1#2.5 (A5), U2#12.5 (A5), U3#11.5 (A5)
Board_3-Net-(U1-A6): U1#2.2 (A6), U2#12.2 (A6), U3#11.2 (A6)
Board_3-Net-(U1-A7): U1#2.4 (A7), U2#12.4 (A7), U3#11.4 (A7)
Board_3-Net-(U1-A): U1#2.3 (A), U2#12.3 (A), U3#11.3 (A)
Board_3-Net-(U1-GND): U1#2.8 (GND), U2#12.8 (GND), U3#11.8 (GND)
Board_3-Net-(U1-S0): U1#2.11 (S0), U2#12.11 (S0), U3#11.11 (S0)
Board_3-Net-(U1-S1): U1#2.10 (S1), U2#12.10 (S1), U3#11.10 (S1)
Board_3-Net-(U1-S2): U1#2.9 (S2), U2#12.9 (S2), U3#11.9 (S2)
Board_3-Net-(U1-VCC): U1#2.16 (VCC), U2#12.16 (VCC), U3#11.16 (VCC)
Board_3-Net-(U1-VEE): U1#2.7 (VEE), U2#12.7 (VEE), U3#11.7 (VEE)
Board_4-Net-(U1-*E): U1#3.6 (*E), U2.6 (*E), U3#7.6 (*E)
Board_4-Net-(U1-A0): U1#3.13 (A0), U2.13 (A0), U3#7.13 (A0)
Board_4-Net-(U1-A1): U1#3.14 (A1), U2.14 (A1), U3#7.14 (A1)
Board_4-Net-(U1-A2): U1#3.15 (A2), U2.15 (A2), U3#7.15 (A2)
Board_4-Net-(U1-A3): U1#3.12 (A3), U2.12 (A3), U3#7.12 (A3)
Board_4-Net-(U1-A4): U1#3.1 (A4), U2.1 (A4), U3#7.1 (A4)
Board_4-Net-(U1-A5): U1#3.5 (A5), U2.5 (A5), U3#7.5 (A5)
Board_4-Net-(U1-A6): U1#3.2 (A6), U2.2 (A6), U3#7.2 (A6)
Board_4-Net-(U1-A7): U1#3.4 (A7), U2.4 (A7), U3#7.4 (A7)
Board_4-Net-(U1-A): U1#3.3 (A), U2.3 (A), U3#7.3 (A)
Board_4-Net-(U1-GND): U1#3.8 (GND), U2.8 (GND), U3#7.8 (GND)
Board_4-Net-(U1-S0): U1#3.11 (S0), U2.11 (S0), U3#7.11 (S0)
Board_4-Net-(U1-S1): U1#3.10 (S1), U2.10 (S1), U3#7.10 (S1)
Board_4-Net-(U1-S2): U1#3.9 (S2), U2.9 (S2), U3#7.9 (S2)
Board_4-Net-(U1-VCC): U1#3.16 (VCC), U2.16 (VCC), U3#7.16 (VCC)
Board_4-Net-(U1-VEE): U1#3.7 (VEE), U2.7 (VEE), U3#7.7 (VEE)
Board_5-Net-(U1-*E): U1#11.6 (*E), U2#7.6 (*E), U3#14.6 (*E)
Board_5-Net-(U1-A0): U1#11.13 (A0), U2#7.13 (A0), U3#14.13 (A0)
Board_5-Net-(U1-A1): U1#11.14 (A1), U2#7.14 (A1), U3#14.14 (A1)
Board_5-Net-(U1-A2): U1#11.15 (A2), U2#7.15 (A2), U3#14.15 (A2)
Board_5-Net-(U1-A3): U1#11.12 (A3), U2#7.12 (A3), U3#14.12 (A3)
Board_5-Net-(U1-A4): U1#11.1 (A4), U2#7.1 (A4), U3#14.1 (A4)
Board_5-Net-(U1-A5): U1#11.5 (A5), U2#7.5 (A5), U3#14.5 (A5)
Board_5-Net-(U1-A6): U1#11.2 (A6), U2#7.2 (A6), U3#14.2 (A6)
Board_5-Net-(U1-A7): U1#11.4 (A7), U2#7.4 (A7), U3#14.4 (A7)
Board_5-Net-(U1-A): U1#11.3 (A), U2#7.3 (A), U3#14.3 (A)
Board_5-Net-(U1-GND): U1#11.8 (GND), U2#7.8 (GND), U3#14.8 (GND)
Board_5-Net-(U1-S0): U1#11.11 (S0), U2#7.11 (S0), U3#14.11 (S0)
Board_5-Net-(U1-S1): U1#11.10 (S1), U2#7.10 (S1), U3#14.10 (S1)
Board_5-Net-(U1-S2): U1#11.9 (S2), U2#7.9 (S2), U3#14.9 (S2)
Board_5-Net-(U1-VCC): U1#11.16 (VCC), U2#7.16 (VCC), U3#14.16 (VCC)
Board_5-Net-(U1-VEE): U1#11.7 (VEE), U2#7.7 (VEE), U3#14.7 (VEE)
Board_6-Net-(U1-*E): U1#14.6 (*E), U2#6.6 (*E), U3#9.6 (*E)
Board_6-Net-(U1-A0): U1#14.13 (A0), U2#6.13 (A0), U3#9.13 (A0)
Board_6-Net-(U1-A1): U1#14.14 (A1), U2#6.14 (A1), U3#9.14 (A1)
Board_6-Net-(U1-A2): U1#14.15 (A2), U2#6.15 (A2), U3#9.15 (A2)
Board_6-Net-(U1-A3): U1#14.12 (A3), U2#6.12 (A3), U3#9.12 (A3)
Board_6-Net-(U1-A4): U1#14.1 (A4), U2#6.1 (A4), U3#9.1 (A4)
Board_6-Net-(U1-A5): U1#14.5 (A5), U2#6.5 (A5), U3#9.5 (A5)
Board_6-Net-(U1-A6): U1#14.2 (A6), U2#6.2 (A6), U3#9.2 (A6)
Board_6-Net-(U1-A7): U1#14.4 (A7), U2#6.4 (A7), U3#9.4 (A7)
Board_6-Net-(U1-A): U1#14.3 (A), U2#6.3 (A), U3#9.3 (A)
Board_6-Net-(U1-GND): U1#14.8 (GND), U2#6.8 (GND), U3#9.8 (GND)
Board_6-Net-(U1-S0): U1#14.11 (S0), U2#6.11 (S0), U3#9.11 (S0)
Board_6-Net-(U1-S1): U1#14.10 (S1), U2#6.10 (S1), U3#9.10 (S1)
Board_6-Net-(U1-S2): U1#14.9 (S2), U2#6.9 (S2), U3#9.9 (S2)
Board_6-Net-(U1-VCC): U1#14.16 (VCC), U2#6.16 (VCC), U3#9.16 (VCC)
Board_6-Net-(U1-VEE): U1#14.7 (VEE), U2#6.7 (VEE), U3#9.7 (VEE)
Board_7-Net-(U1-*E): U1#7.6 (*E), U2#4.6 (*E), U3#5.6 (*E)
Board_7-Net-(U1-A0): U1#7.13 (A0), U2#4.13 (A0), U3#5.13 (A0)
Board_7-Net-(U1-A1): U1#7.14 (A1), U2#4.14 (A1), U3#5.14 (A1)
Board_7-Net-(U1-A2): U1#7.15 (A2), U2#4.15 (A2), U3#5.15 (A2)
Board_7-Net-(U1-A3): U1#7.12 (A3), U2#4.12 (A3), U3#5.12 (A3)
Board_7-Net-(U1-A4): U1#7.1 (A4), U2#4.1 (A4), U3#5.1 (A4)
Board_7-Net-(U1-A5): U1#7.5 (A5), U2#4.5 (A5), U3#5.5 (A5)
Board_7-Net-(U1-A6): U1#7.2 (A6), U2#4.2 (A6), U3#5.2 (A6)
Board_7-Net-(U1-A7): U1#7.4 (A7), U2#4.4 (A7), U3#5.4 (A7)
Board_7-Net-(U1-A): U1#7.3 (A), U2#4.3 (A), U3#5.3 (A)
Board_7-Net-(U1-GND): U1#7.8 (GND), U2#4.8 (GND), U3#5.8 (GND)
Board_7-Net-(U1-S0): U1#7.11 (S0), U2#4.11 (S0), U3#5.11 (S0)
Board_7-Net-(U1-S1): U1#7.10 (S1), U2#4.10 (S1), U3#5.10 (S1)
Board_7-Net-(U1-S2): U1#7.9 (S2), U2#4.9 (S2), U3#5.9 (S2)
Board_7-Net-(U1-VCC): U1#7.16 (VCC), U2#4.16 (VCC), U3#5.16 (VCC)
Board_7-Net-(U1-VEE): U1#7.7 (VEE), U2#4.7 (VEE), U3#5.7 (VEE)
Board_8-Net-(U1-*E): U1#13.6 (*E), U2#11.6 (*E), U3#10.6 (*E)
Board_8-Net-(U1-A0): U1#13.13 (A0), U2#11.13 (A0), U3#10.13 (A0)
Board_8-Net-(U1-A1): U1#13.14 (A1), U2#11.14 (A1), U3#10.14 (A1)
Board_8-Net-(U1-A2): U1#13.15 (A2), U2#11.15 (A2), U3#10.15 (A2)
Board_8-Net-(U1-A3): U1#13.12 (A3), U2#11.12 (A3), U3#10.12 (A3)
Board_8-Net-(U1-A4): U1#13.1 (A4), U2#11.1 (A4), U3#10.1 (A4)
Board_8-Net-(U1-A5): U1#13.5 (A5), U2#11.5 (A5), U3#10.5 (A5)
Board_8-Net-(U1-A6): U1#13.2 (A6), U2#11.2 (A6), U3#10.2 (A6)
Board_8-Net-(U1-A7): U1#13.4 (A7), U2#11.4 (A7), U3#10.4 (A7)
Board_8-Net-(U1-A): U1#13.3 (A), U2#11.3 (A), U3#10.3 (A)
Board_8-Net-(U1-GND): U1#13.8 (GND), U2#11.8 (GND), U3#10.8 (GND)
Board_8-Net-(U1-S0): U1#13.11 (S0), U2#11.11 (S0), U3#10.11 (S0)
Board_8-Net-(U1-S1): U1#13.10 (S1), U2#11.10 (S1), U3#10.10 (S1)
Board_8-Net-(U1-S2): U1#13.9 (S2), U2#11.9 (S2), U3#10.9 (S2)
Board_8-Net-(U1-VCC): U1#13.16 (VCC), U2#11.16 (VCC), U3#10.16 (VCC)
Board_8-Net-(U1-VEE): U1#13.7 (VEE), U2#11.7 (VEE), U3#10.7 (VEE)
Board_9-Net-(U1-*E): U1#12.6 (*E), U2#5.6 (*E), U3#12.6 (*E)
Board_9-Net-(U1-A0): U1#12.13 (A0), U2#5.13 (A0), U3#12.13 (A0)
Board_9-Net-(U1-A1): U1#12.14 (A1), U2#5.14 (A1), U3#12.14 (A1)
Board_9-Net-(U1-A2): U1#12.15 (A2), U2#5.15 (A2), U3#12.15 (A2)
Board_9-Net-(U1-A3): U1#12.12 (A3), U2#5.12 (A3), U3#12.12 (A3)
Board_9-Net-(U1-A4): U1#12.1 (A4), U2#5.1 (A4), U3#12.1 (A4)
Board_9-Net-(U1-A5): U1#12.5 (A5), U2#5.5 (A5), U3#12.5 (A5)
Board_9-Net-(U1-A6): U1#12.2 (A6), U2#5.2 (A6), U3#12.2 (A6)
Board_9-Net-(U1-A7): U1#12.4 (A7), U2#5.4 (A7), U3#12.4 (A7)
Board_9-Net-(U1-A): U1#12.3 (A), U2#5.3 (A), U3#12.3 (A)
Board_9-Net-(U1-GND): U1#12.8 (GND), U2#5.8 (GND), U3#12.8 (GND)
Board_9-Net-(U1-S0): U1#12.11 (S0), U2#5.11 (S0), U3#12.11 (S0)
Board_9-Net-(U1-S1): U1#12.10 (S1), U2#5.10 (S1), U3#12.10 (S1)
Board_9-Net-(U1-S2): U1#12.9 (S2), U2#5.9 (S2), U3#12.9 (S2)
Board_9-Net-(U1-VCC): U1#12.16 (VCC), U2#5.16 (VCC), U3#12.16 (VCC)
Board_9-Net-(U1-VEE): U1#12.7 (VEE), U2#5.7 (VEE), U3#12.7 (VEE)
Board_10-Net-(U1-*E): U1.6 (*E), U2#13.6 (*E), U3#8.6 (*E)
Board_10-Net-(U1-A0): U1.13 (A0), U2#13.13 (A0), U3#8.13 (A0)
Board_10-Net-(U1-A1): U1.14 (A1), U2#13.14 (A1), U3#8.14 (A1)
Board_10-Net-(U1-A2): U1.15 (A2), U2#13.15 (A2), U3#8.15 (A2)
Board_10-Net-(U1-A3): U1.12 (A3), U2#13.12 (A3), U3#8.12 (A3)
Board_10-Net-(U1-A4): U1.1 (A4), U2#13.1 (A4), U3#8.1 (A4)
Board_10-Net-(U1-A5): U1.5 (A5), U2#13.5 (A5), U3#8.5 (A5)
Board_10-Net-(U1-A6): U1.2 (A6), U2#13.2 (A6), U3#8.2 (A6)
Board_10-Net-(U1-A7): U1.4 (A7), U2#13.4 (A7), U3#8.4 (A7)
Board_10-Net-(U1-A): U1.3 (A), U2#13.3 (A), U3#8.3 (A)
Board_10-Net-(U1-GND): U1.8 (GND), U2#13.8 (GND), U3#8.8 (GND)
Board_10-Net-(U1-S0): U1.11 (S0), U2#13.11 (S0), U3#8.11 (S0)
Board_10-Net-(U1-S1): U1.10 (S1), U2#13.10 (S1), U3#8.10 (S1)
Board_10-Net-(U1-S2): U1.9 (S2), U2#13.9 (S2), U3#8.9 (S2)
Board_10-Net-(U1-VCC): U1.16 (VCC), U2#13.16 (VCC), U3#8.16 (VCC)
Board_10-Net-(U1-VEE): U1.7 (VEE), U2#13.7 (VEE), U3#8.7 (VEE)
Board_11-Net-(U1-*E): U1#6.6 (*E), U2#15.6 (*E), U3#4.6 (*E)
Board_11-Net-(U1-A0): U1#6.13 (A0), U2#15.13 (A0), U3#4.13 (A0)
Board_11-Net-(U1-A1): U1#6.14 (A1), U2#15.14 (A1), U3#4.14 (A1)
Board_11-Net-(U1-A2): U1#6.15 (A2), U2#15.15 (A2), U3#4.15 (A2)
Board_11-Net-(U1-A3): U1#6.12 (A3), U2#15.12 (A3), U3#4.12 (A3)
Board_11-Net-(U1-A4): U1#6.1 (A4), U2#15.1 (A4), U3#4.1 (A4)
Board_11-Net-(U1-A5): U1#6.5 (A5), U2#15.5 (A5), U3#4.5 (A5)
Board_11-Net-(U1-A6): U1#6.2 (A6), U2#15.2 (A6), U3#4.2 (A6)
Board_11-Net-(U1-A7): U1#6.4 (A7), U2#15.4 (A7), U3#4.4 (A7)
Board_11-Net-(U1-A): U1#6.3 (A), U2#15.3 (A), U3#4.3 (A)
Board_11-Net-(U1-GND): U1#6.8 (GND), U2#15.8 (GND), U3#4.8 (GND)
Board_11-Net-(U1-S0): U1#6.11 (S0), U2#15.11 (S0), U3#4.11 (S0)
Board_11-Net-(U1-S1): U1#6.10 (S1), U2#15.10 (S1), U3#4.10 (S1)
Board_11-Net-(U1-S2): U1#6.9 (S2), U2#15.9 (S2), U3#4.9 (S2)
Board_11-Net-(U1-VCC): U1#6.16 (VCC), U2#15.16 (VCC), U3#4.16 (VCC)
Board_11-Net-(U1-VEE): U1#6.7 (VEE), U2#15.7 (VEE), U3#4.7 (VEE)
Board_12-Net-(U1-*E): U1#15.6 (*E), U2#16.6 (*E), U3#15.6 (*E)
Board_12-Net-(U1-A0): U1#15.13 (A0), U2#16.13 (A0), U3#15.13 (A0)
Board_12-Net-(U1-A1): U1#15.14 (A1), U2#16.14 (A1), U3#15.14 (A1)
Board_12-Net-(U1-A2): U1#15.15 (A2), U2#16.15 (A2), U3#15.15 (A2)
Board_12-Net-(U1-A3): U1#15.12 (A3), U2#16.12 (A3), U3#15.12 (A3)
Board_12-Net-(U1-A4): U1#15.1 (A4), U2#16.1 (A4), U3#15.1 (A4)
Board_12-Net-(U1-A5): U1#15.5 (A5), U2#16.5 (A5), U3#15.5 (A5)
Board_12-Net-(U1-A6): U1#15.2 (A6), U2#16.2 (A6), U3#15.2 (A6)
Board_12-Net-(U1-A7): U1#15.4 (A7), U2#16.4 (A7), U3#15.4 (A7)
Board_12-Net-(U1-A): U1#15.3 (A), U2#16.3 (A), U3#15.3 (A)
Board_12-Net-(U1-GND): U1#15.8 (GND), U2#16.8 (GND), U3#15.8 (GND)
Board_12-Net-(U1-S0): U1#15.11 (S0), U2#16.11 (S0), U3#15.11 (S0)
Board_12-Net-(U1-S1): U1#15.10 (S1), U2#16.10 (S1), U3#15.10 (S1)
Board_12-Net-(U1-S2): U1#15.9 (S2), U2#16.9 (S2), U3#15.9 (S2)
Board_12-Net-(U1-VCC): U1#15.16 (VCC), U2#16.16 (VCC), U3#15.16 (VCC)
Board_12-Net-(U1-VEE): U1#15.7 (VEE), U2#16.7 (VEE), U3#15.7 (VEE)
Board_13-Net-(U1-*E): U1#8.6 (*E), U2#2.6 (*E), U3#16.6 (*E)
Board_13-Net-(U1-A0): U1#8.13 (A0), U2#2.13 (A0), U3#16.13 (A0)
Board_13-Net-(U1-A1): U1#8.14 (A1), U2#2.14 (A1), U3#16.14 (A1)
Board_13-Net-(U1-A2): U1#8.15 (A2), U2#2.15 (A2), U3#16.15 (A2)
Board_13-Net-(U1-A3): U1#8.12 (A3), U2#2.12 (A3), U3#16.12 (A3)
Board_13-Net-(U1-A4): U1#8.1 (A4), U2#2.1 (A4), U3#16.1 (A4)
Board_13-Net-(U1-A5): U1#8.5 (A5), U2#2.5 (A5), U3#16.5 (A5)
Board_13-Net-(U1-A6): U1#8.2 (A6), U2#2.2 (A6), U3#16.2 (A6)
Board_13-Net-(U1-A7): U1#8.4 (A7), U2#2.4 (A7), U3#16.4 (A7)
Board_13-Net-(U1-A): U1#8.3 (A), U2#2.3 (A), U3#16.3 (A)
Board_13-Net-(U1-GND): U1#8.8 (GND), U2#2.8 (GND), U3#16.8 (GND)
Board_13-Net-(U1-S0): U1#8.11 (S0), U2#2.11 (S0), U3#16.11 (S0)
Board_13-Net-(U1-S1): U1#8.10 (S1), U2#2.10 (S1), U3#16.10 (S1)
Board_13-Net-(U1-S2): U1#8.9 (S2), U2#2.9 (S2), U3#16.9 (S2)
Board_13-Net-(U1-VCC): U1#8.16 (VCC), U2#2.16 (VCC), U3#16.16 (VCC)
Board_13-Net-(U1-VEE): U1#8.7 (VEE), U2#2.7 (VEE), U3#16.7 (VEE)
Board_14-Net-(U1-*E): U1#9.6 (*E), U2#10.6 (*E), U3#3.6 (*E)
Board_14-Net-(U1-A0): U1#9.13 (A0), U2#10.13 (A0), U3#3.13 (A0)
Board_14-Net-(U1-A1): U1#9.14 (A1), U2#10.14 (A1), U3#3.14 (A1)
Board_14-Net-(U1-A2): U1#9.15 (A2), U2#10.15 (A2), U3#3.15 (A2)
Board_14-Net-(U1-A3): U1#9.12 (A3), U2#10.12 (A3), U3#3.12 (A3)
Board_14-Net-(U1-A4): U1#9.1 (A4), U2#10.1 (A4), U3#3.1 (A4)
Board_14-Net-(U1-A5): U1#9.5 (A5), U2#10.5 (A5), U3#3.5 (A5)
Board_14-Net-(U1-A6): U1#9.2 (A6), U2#10.2 (A6), U3#3.2 (A6)
Board_14-Net-(U1-A7): U1#9.4 (A7), U2#10.4 (A7), U3#3.4 (A7)
Board_14-Net-(U1-A): U1#9.3 (A), U2#10.3 (A), U3#3.3 (A)
Board_14-Net-(U1-GND): U1#9.8 (GND), U2#10.8 (GND), U3#3.8 (GND)
Board_14-Net-(U1-S0): U1#9.11 (S0), U2#10.11 (S0), U3#3.11 (S0)
Board_14-Net-(U1-S1): U1#9.10 (S1), U2#10.10 (S1), U3#3.10 (S1)
Board_14-Net-(U1-S2): U1#9.9 (S2), U2#10.9 (S2), U3#3.9 (S2)
Board_14-Net-(U1-VCC): U1#9.16 (VCC), U2#10.16 (VCC), U3#3.16 (VCC)
Board_14-Net-(U1-VEE): U1#9.7 (VEE), U2#10.7 (VEE), U3#3.7 (VEE)
Board_15-Net-(U1-*E): U1#4.6 (*E), U2#3.6 (*E), U3#2.6 (*E)
Board_15-Net-(U1-A0): U1#4.13 (A0), U2#3.13 (A0), U3#2.13 (A0)
Board_15-Net-(U1-A1): U1#4.14 (A1), U2#3.14 (A1), U3#2.14 (A1)
Board_15-Net-(U1-A2): U1#4.15 (A2), U2#3.15 (A2), U3#2.15 (A2)
Board_15-Net-(U1-A3): U1#4.12 (A3), U2#3.12 (A3), U3#2.12 (A3)
Board_15-Net-(U1-A4): U1#4.1 (A4), U2#3.1 (A4), U3#2.1 (A4)
Board_15-Net-(U1-A5): U1#4.5 (A5), U2#3.5 (A5), U3#2.5 (A5)
Board_15-Net-(U1-A6): U1#4.2 (A6), U2#3.2 (A6), U3#2.2 (A6)
Board_15-Net-(U1-A7): U1#4.4 (A7), U2#3.4 (A7), U3#2.4 (A7)
Board_15-Net-(U1-A): U1#4.3 (A), U2#3.3 (A), U3#2.3 (A)
Board_15-Net-(U1-GND): U1#4.8 (GND), U2#3.8 (GND), U3#2.8 (GND)
Board_15-Net-(U1-S0): U1#4.11 (S0), U2#3.11 (S0), U3#2.11 (S0)
Board_15-Net-(U1-S1): U1#4.10 (S1), U2#3.10 (S1), U3#2.10 (S1)
Board_15-Net-(U1-S2): U1#4.9 (S2), U2#3.9 (S2), U3#2.9 (S2)
Board_15-Net-(U1-VCC): U1#4.16 (VCC), U2#3.16 (VCC), U3#2.16 (VCC)
Board_15-Net-(U1-VEE): U1#4.7 (VEE), U2#3.7 (VEE), U3#2.7 (VEE)
